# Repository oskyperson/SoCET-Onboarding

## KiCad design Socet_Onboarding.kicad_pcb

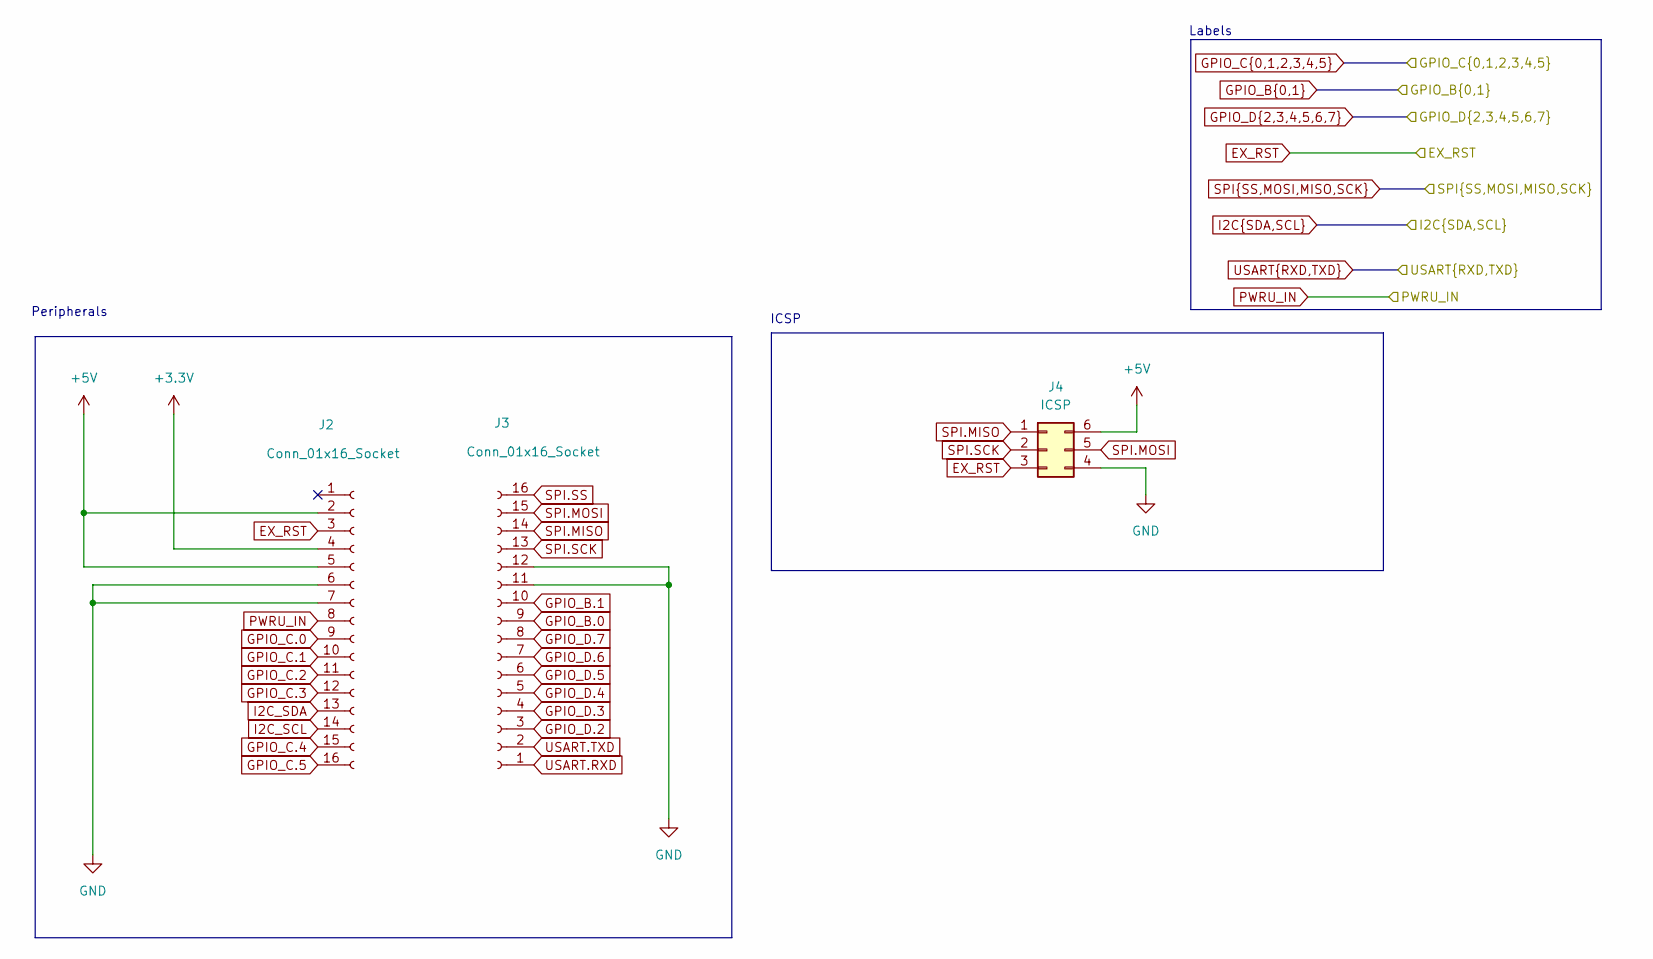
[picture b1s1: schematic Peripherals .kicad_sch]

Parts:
J2, J3: Conn_01x16_Socket; PinHeader_1x16_P2.54mm_Vertical
J4: ICSP; PinSocket_2x03_P2.54mm_Vertical

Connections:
+3.3V: J2.4; also elsewhere on the board
+5V: J2.2, J2.5, J4.6; also elsewhere on the board
EX_RST: J2.3, J4.3; also elsewhere on the board
GND: J2.6, J2.7, J3.11, J3.12, J4.4; also elsewhere on the board
GPIO_B.0: J3.9; also elsewhere on the board
GPIO_B.1: J3.10; also elsewhere on the board
GPIO_C.0: J2.9; also elsewhere on the board
GPIO_C.1: J2.10; also elsewhere on the board
GPIO_C.2: J2.11; also elsewhere on the board
GPIO_C.3: J2.12; also elsewhere on the board
GPIO_C.4: J2.15; also elsewhere on the board
GPIO_C.5: J2.16; also elsewhere on the board
GPIO_D.2: J3.3; also elsewhere on the board
GPIO_D.3: J3.4; also elsewhere on the board
GPIO_D.4: J3.5; also elsewhere on the board
GPIO_D.5: J3.6; also elsewhere on the board
GPIO_D.6: J3.7; also elsewhere on the board
GPIO_D.7: J3.8; also elsewhere on the board
I2C_SCL: J2.14; also elsewhere on the board
I2C_SDA: J2.13; also elsewhere on the board
PWRU_IN: J2.8; also elsewhere on the board
SPI.MISO: J3.14, J4.1; also elsewhere on the board
SPI.MOSI: J3.15, J4.5; also elsewhere on the board
SPI.SCK: J3.13, J4.2; also elsewhere on the board
SPI.SS: J3.16; also elsewhere on the board
USART.RXD: J3.1; also elsewhere on the board
USART.TXD: J3.2; also elsewhere on the board

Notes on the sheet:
Peripherals
ICSP
Labels

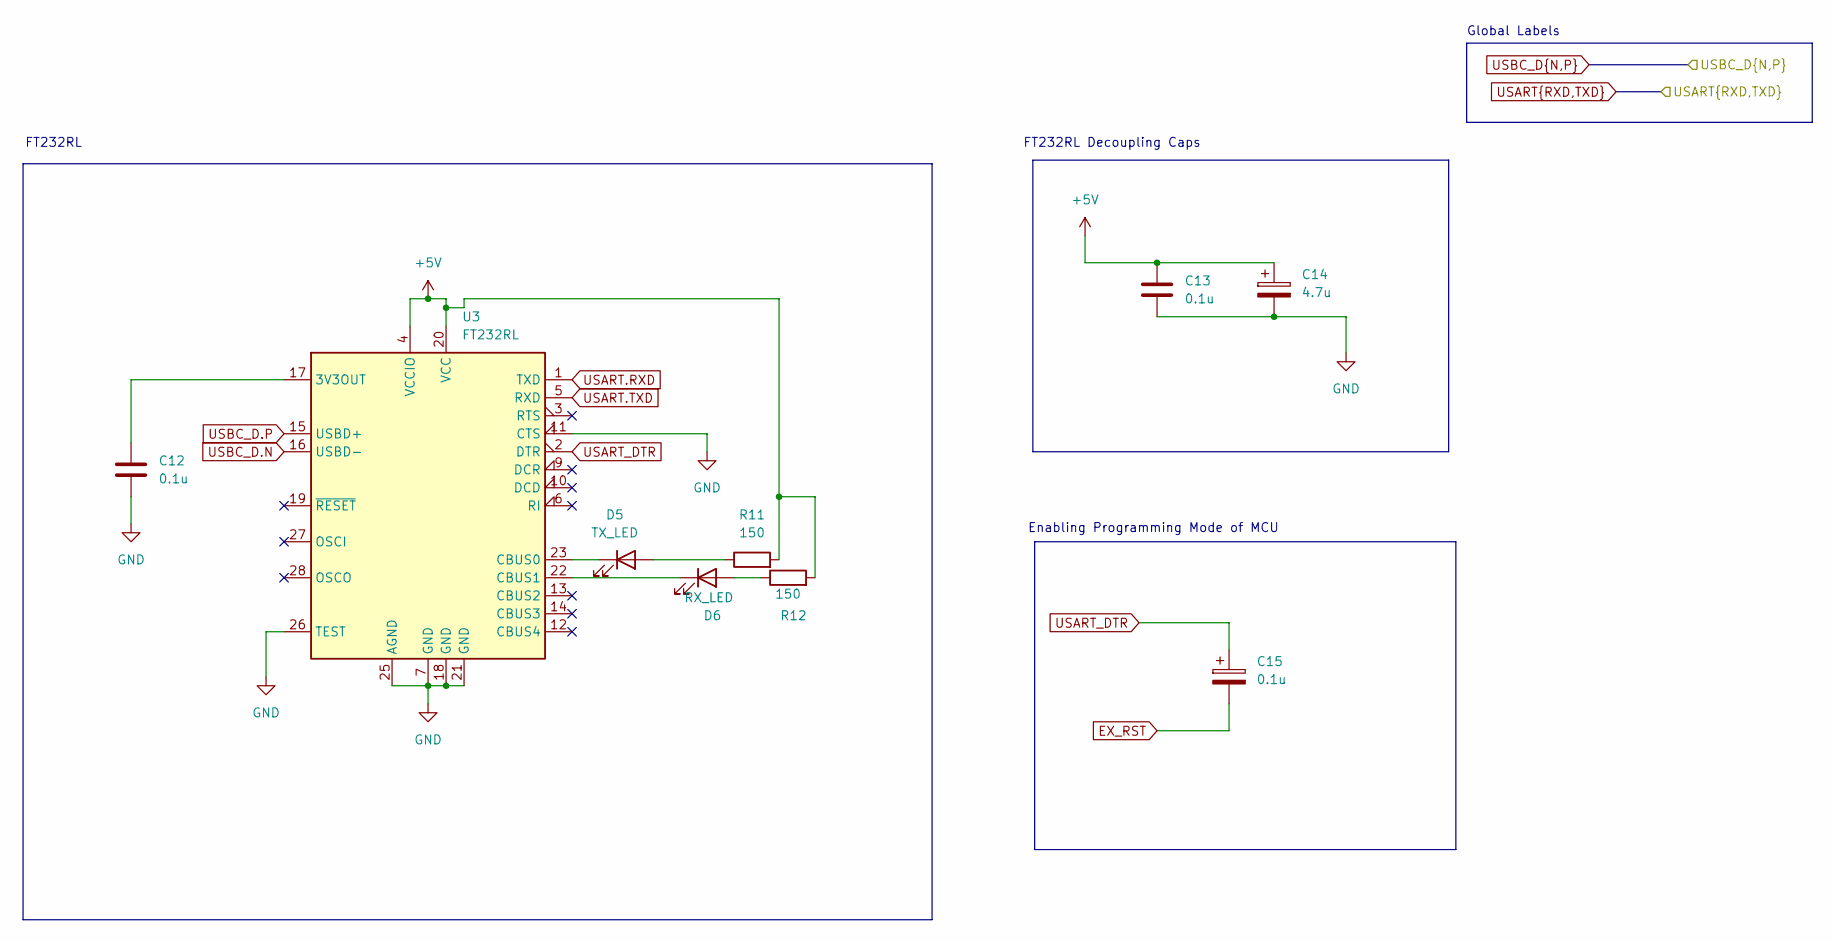
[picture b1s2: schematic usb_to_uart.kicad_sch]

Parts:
C12, C13: 0.1u; C_0402_1005Metric
C14: 4.7u; CP_Elec_6.3x7.7
C15: 0.1u; CP_Elec_6.3x7.7
D5: TX_LED; LED_0402_1005Metric
D6: RX_LED; LED_0402_1005Metric
R11, R12: 150; R_0402_1005Metric
U3: FT232RL; SSOP-28_5.3x10.2mm_P0.65mm

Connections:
+5V: C13.1, C14.1, R11.2, R12.2, U3.4 (VCCIO), U3.20 (VCC); also elsewhere on the board
EX_RST: C15.2; also elsewhere on the board
GND: C12.2, C13.2, C14.2, U3.7 (GND), U3.11 (CTS), U3.18 (GND), U3.21 (GND), U3.25 (AGND), U3.26 (TEST); also elsewhere on the board
unnamed: D5.2 (A), R11.1
unnamed: D5.1 (K), U3.23 (CBUS0)
unnamed: D6.2 (A), R12.1
unnamed: D6.1 (K), U3.22 (CBUS1)
unnamed: C12.1, U3.17 (3V3OUT)
USART.RXD: U3.1 (TXD); also elsewhere on the board
USART.TXD: U3.5 (RXD); also elsewhere on the board
USART_DTR: C15.1, U3.2 (DTR)
USBC_D.N: U3.16 (USBD-); also elsewhere on the board
USBC_D.P: U3.15 (USBD+); also elsewhere on the board

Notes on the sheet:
Enabling Programming Mode of MCU
Global Labels
FT232RL Decoupling Caps
FT232RL

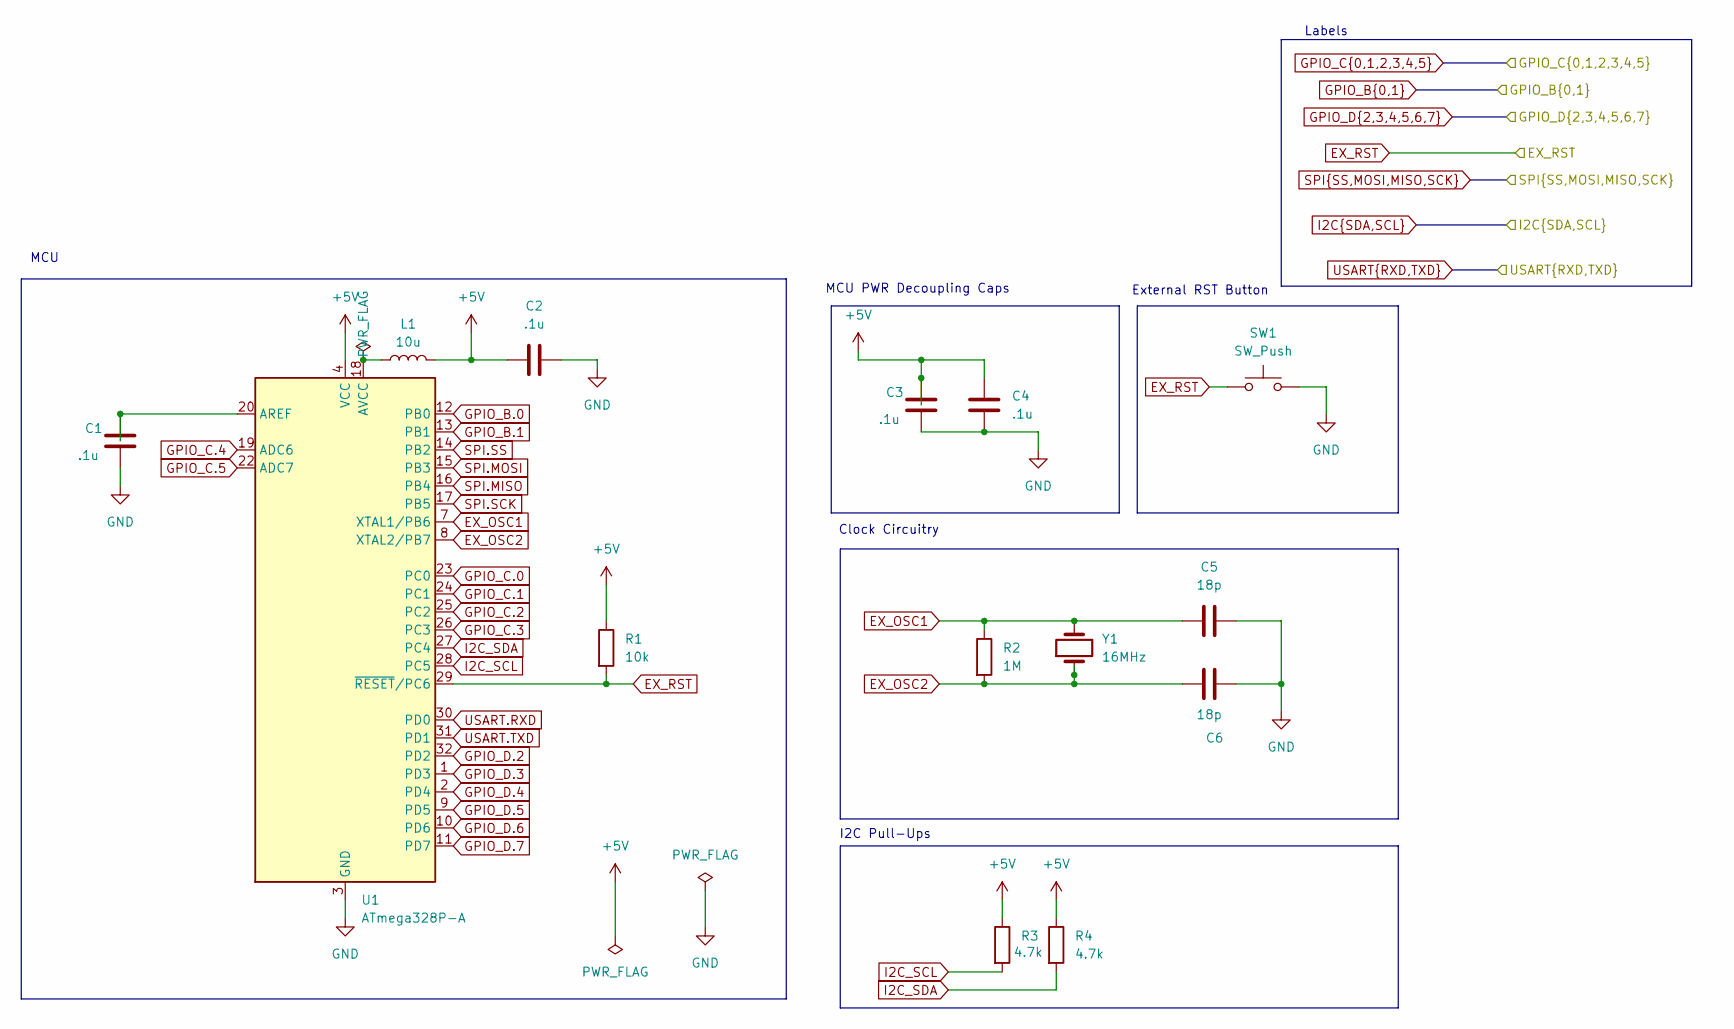
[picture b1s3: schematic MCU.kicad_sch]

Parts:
C1, C2, C3, C4: .1u; C_0402_1005Metric
C5, C6: 18p; C_0402_1005Metric
L1: 10u; L_0603_1608Metric
R1: 10k; R_0402_1005Metric
R2: 1M; R_0402_1005Metric
R3, R4: 4.7k; R_0402_1005Metric
SW1: SW_Push; SW_Push_SPST_NO_Alps_SKRK
U1: ATmega328P-A; TQFP-32_7x7mm_P0.8mm
Y1: 16MHz; Crystal_SMD_2012-2Pin_2.0x1.2mm

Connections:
+5V: C2.1, C3.2, C4.1, L1.2, R1.1, R3.1, R4.1, U1.4 (VCC), U1.6 (VCC); also elsewhere on the board
EX_OSC1: C5.2, R2.1, U1.7 (XTAL1/PB6), Y1.2
EX_OSC2: C6.2, R2.2, U1.8 (XTAL2/PB7), Y1.1
EX_RST: R1.2, SW1.1, U1.29 (~RESET/PC6); also elsewhere on the board
GND: C1.1, C2.2, C3.1, C4.2, C5.1, C6.1, SW1.2, U1.3 (GND), U1.5 (GND), U1.21 (GND); also elsewhere on the board
GPIO_B.0: U1.12 (PB0); also elsewhere on the board
GPIO_B.1: U1.13 (PB1); also elsewhere on the board
GPIO_C.0: U1.23 (PC0); also elsewhere on the board
GPIO_C.1: U1.24 (PC1); also elsewhere on the board
GPIO_C.2: U1.25 (PC2); also elsewhere on the board
GPIO_C.3: U1.26 (PC3); also elsewhere on the board
GPIO_C.4: U1.19 (ADC6); also elsewhere on the board
GPIO_C.5: U1.22 (ADC7); also elsewhere on the board
GPIO_D.2: U1.32 (PD2); also elsewhere on the board
GPIO_D.3: U1.1 (PD3); also elsewhere on the board
GPIO_D.4: U1.2 (PD4); also elsewhere on the board
GPIO_D.5: U1.9 (PD5); also elsewhere on the board
GPIO_D.6: U1.10 (PD6); also elsewhere on the board
GPIO_D.7: U1.11 (PD7); also elsewhere on the board
I2C_SCL: R3.2, U1.28 (PC5); also elsewhere on the board
I2C_SDA: R4.2, U1.27 (PC4); also elsewhere on the board
unnamed: C1.2, U1.20 (AREF)
unnamed: L1.1, U1.18 (AVCC)
SPI.MISO: U1.16 (PB4); also elsewhere on the board
SPI.MOSI: U1.15 (PB3); also elsewhere on the board
SPI.SCK: U1.17 (PB5); also elsewhere on the board
SPI.SS: U1.14 (PB2); also elsewhere on the board
USART.RXD: U1.30 (PD0); also elsewhere on the board
USART.TXD: U1.31 (PD1); also elsewhere on the board

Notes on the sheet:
I2C Pull-Ups
MCU
Labels
MCU PWR Decoupling Caps
Clock Circuitry
External RST Button

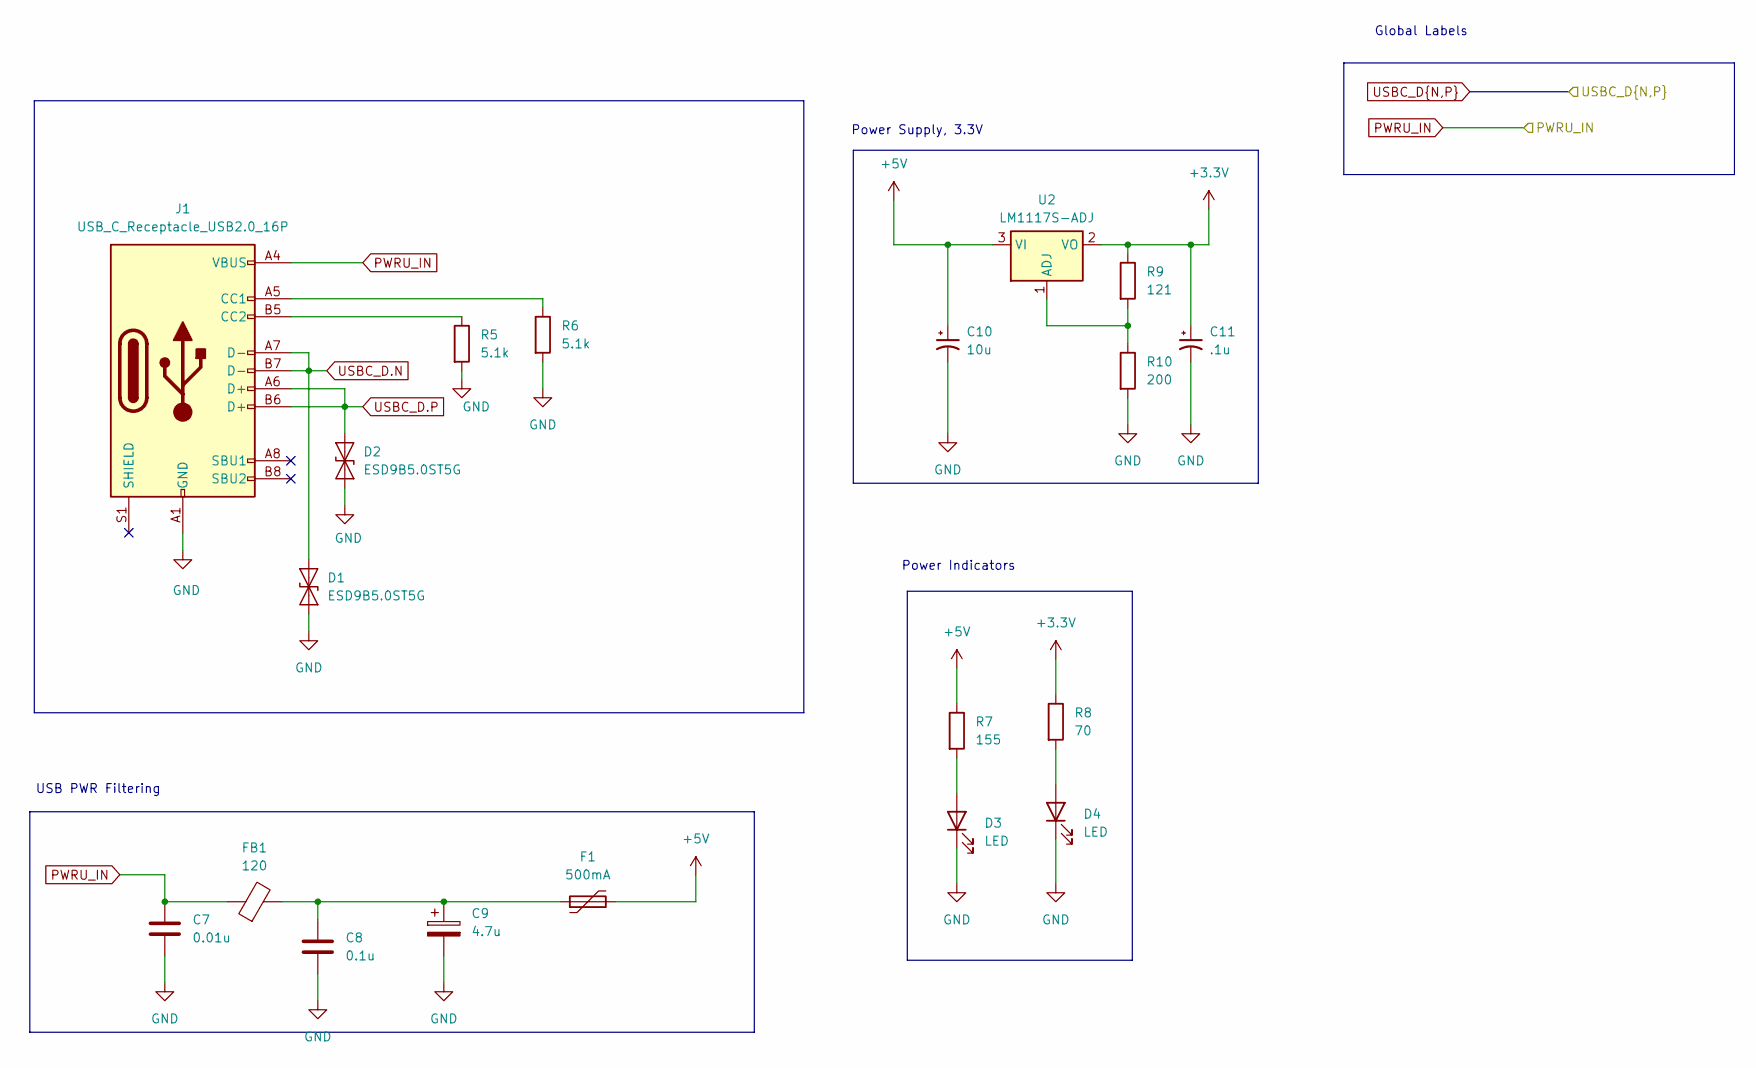
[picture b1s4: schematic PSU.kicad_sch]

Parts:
C7: 0.01u; C_0603_1608Metric
C8: 0.1u; C_0402_1005Metric
C9: 4.7u; CP_Elec_6.3x7.7
C10: 10u; CP_Elec_6.3x7.7
C11: .1u; CP_Elec_6.3x7.7
D1, D2: ESD9B5.0ST5G; D_SOD-923
D3, D4: LED; LED_0402_1005Metric
F1: 500mA; Fuse_1812_4532Metric
FB1: 120; L_0603_1608Metric
J1: USB_C_Receptacle_USB2.0_16P; USB_C_Receptacle_Palconn_UTC16-G
R5, R6: 5.1k; R_0402_1005Metric
R7: 155; R_0402_1005Metric
R8: 70; R_0402_1005Metric
R9: 121; R_0402_1005Metric
R10: 200; R_0402_1005Metric
U2: LM1117S-ADJ; SOT-223

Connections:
+3.3V: C11.1, R8.1, R9.1, U2.2 (VO); also elsewhere on the board
+5V: C10.1, F1.2, R7.1, U2.3 (VI); also elsewhere on the board
GND: C7.1, C8.1, C9.2, C10.2, C11.2, D1.1 (A1), D2.1 (A1), D3.1 (K), D4.1 (K), J1.A1 (GND), J1.A12 (GND), J1.B1 (GND), J1.B12 (GND), R5.2, R6.2, R10.2; also elsewhere on the board
unnamed: C8.2, C9.1, F1.1, FB1.2
unnamed: D3.2 (A), R7.2
unnamed: D4.2 (A), R8.2
unnamed: J1.A5 (CC1), R6.1
unnamed: J1.B5 (CC2), R5.1
unnamed: R9.2, R10.1, U2.1 (ADJ)
PWRU_IN: C7.2, FB1.1, J1.A4 (VBUS), J1.A9 (VBUS), J1.B4 (VBUS), J1.B9 (VBUS); also elsewhere on the board
USBC_D.N: D1.2 (A2), J1.A7 (D-), J1.B7 (D-); also elsewhere on the board
USBC_D.P: D2.2 (A2), J1.A6 (D+), J1.B6 (D+); also elsewhere on the board

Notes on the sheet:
Power Supply, 3.3V
Power Indicators
USB PWR Filtering
Global Labels

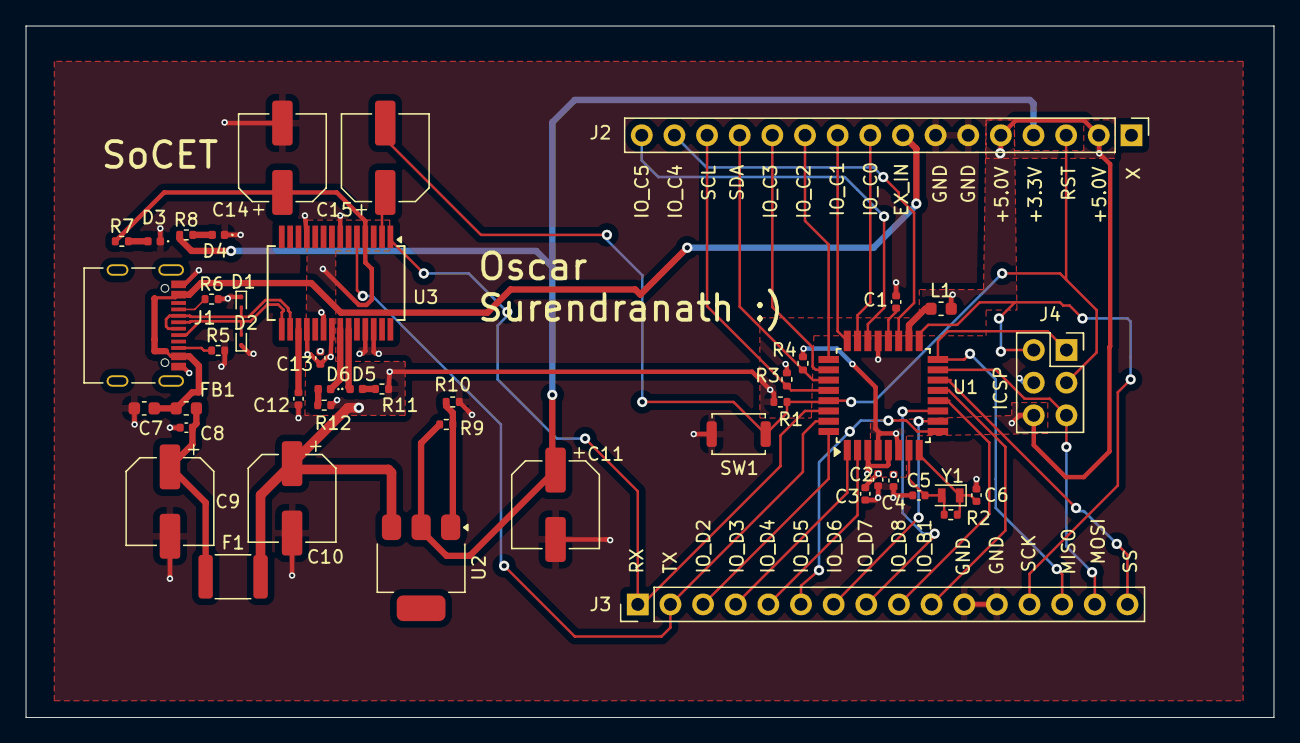
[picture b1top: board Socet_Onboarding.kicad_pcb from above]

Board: 2 copper layers, 97.1 x 53.8 mm, 45 parts (0 on the bottom side), 45 nets.

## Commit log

2025-02-09 Pls check :)
2025-02-09 0 Errors except the ones to ignore I think 0 warnings
